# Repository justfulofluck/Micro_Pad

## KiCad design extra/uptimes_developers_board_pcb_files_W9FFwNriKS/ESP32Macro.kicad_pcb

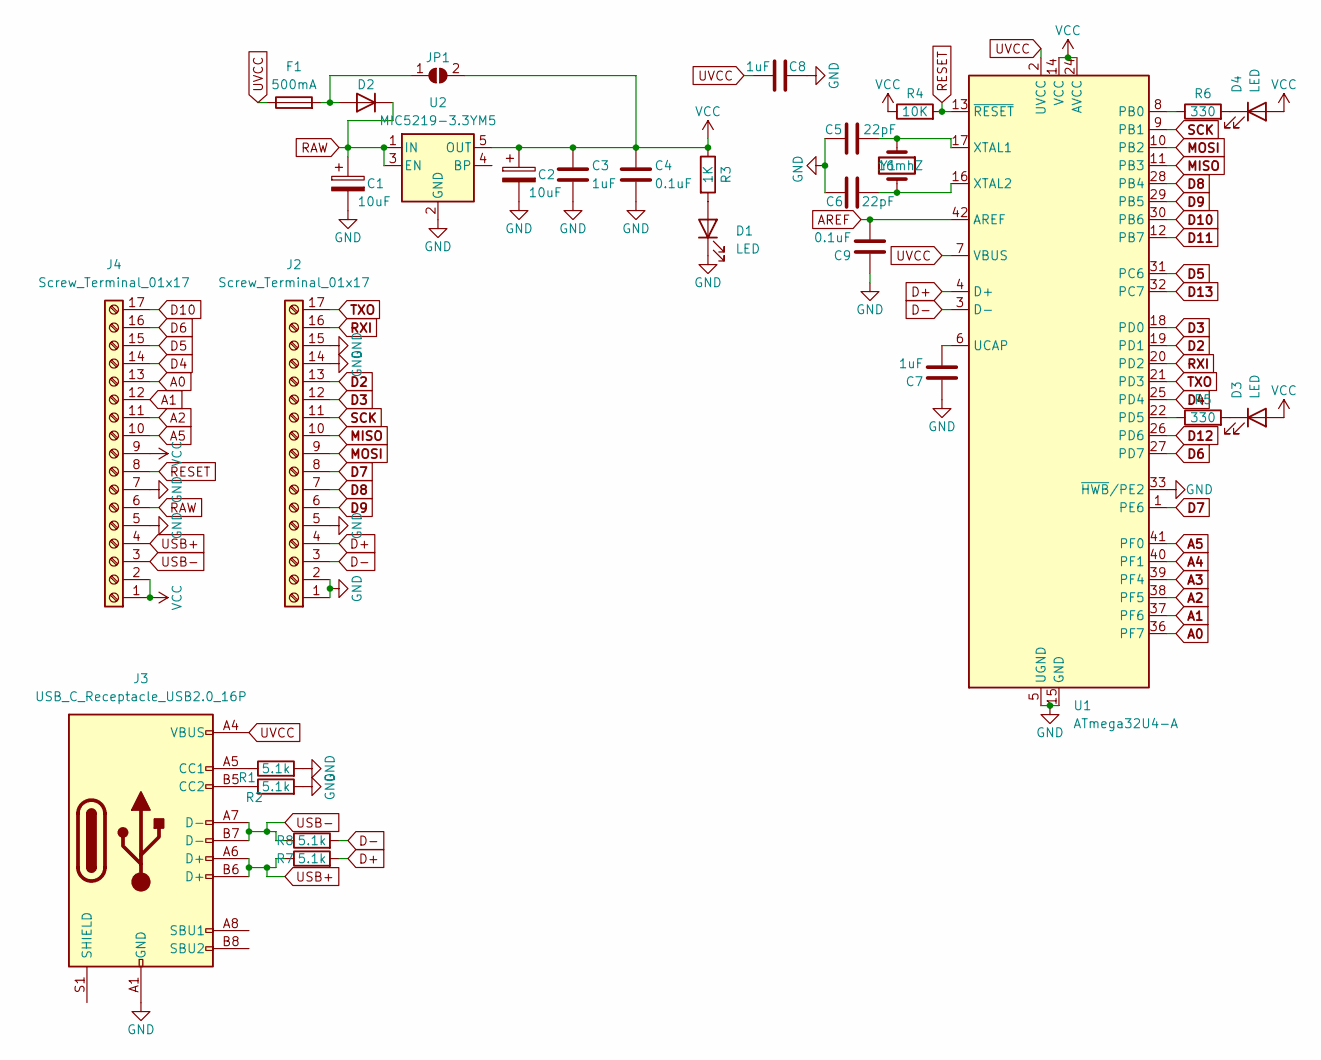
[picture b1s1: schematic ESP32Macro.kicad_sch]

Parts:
C1, C2: 10uF; CP_EIA-3216-18_Kemet-A
C3, C7, C8: 1uF; C_0402_1005Metric
C4, C9: 0.1uF; C_0402_1005Metric
C5, C6: 22pF; C_0402_1005Metric
D1, D3, D4: LED; LED_0805_2012Metric
D2: 1N4148WS; D_SOD-323
F1: 500mA; Fuse_1206_3216Metric
J2, J4: Screw_Terminal_01x17; PinHeader_1x17_P2.54mm_Vertical
J3: USB_C_Receptacle_USB2.0_16P; USB_C_Receptacle_GCT_USB4105-xx-A_16P_TopMnt_Horizontal
JP1: SolderJumper_2_Open; SolderJumper-2_P1.3mm_Open_RoundedPad1.0x1.5mm
R1, R2, R7, R8: 5.1k; R_0402_1005Metric
R3: 1K; R_0402_1005Metric
R4: 10K; R_0402_1005Metric
R5, R6: 330; R_0402_1005Metric
U1: ATmega32U4-A; TQFP-44_10x10mm_P0.8mm
U2: MIC5219-3.3YM5; SOT-23-5
Y1: 16mhZ; Crystal_SMD_3215-2Pin_3.2x1.5mm

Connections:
A0: J4.13, U1.36 (PF7)
A1: J4.12, U1.37 (PF6)
A2: J4.11, U1.38 (PF5)
A3: U1.39 (PF4)
A4: U1.40 (PF1)
A5: J4.10, U1.41 (PF0)
AREF: C9.2, U1.42 (AREF)
D2: J2.13, U1.19 (PD1)
D3: J2.12, U1.18 (PD0)
D4: J4.14, U1.25 (PD4)
D5: J4.15, U1.31 (PC6)
D6: J4.16, U1.27 (PD7)
D7: J2.8, U1.1 (PE6)
D8: J2.7, U1.28 (PB4)
D9: J2.6, U1.29 (PB5)
D10: J4.17, U1.30 (PB6)
D11: U1.12 (PB7)
D12: U1.26 (PD6)
D13: U1.32 (PC7)
D+: J2.4, R7.2, U1.4 (D+)
D-: J2.3, R8.2, U1.3 (D-)
GND: C1.2, C2.2, C3.2, C4.2, C5.1, C6.2, C7.1, C8.2, C9.1, D1.1 (K), J2.1, J2.2, J2.5, J2.14, J2.15, J3.A1 (GND), J3.A12 (GND), J3.B1 (GND), J3.B12 (GND), J4.5, J4.7, R1.2, R2.2, U1.5 (UGND), U1.15 (GND), U1.23 (GND), U1.33 (~HWB/PE2), U1.35 (GND), U1.43 (GND), U2.2 (GND)
MISO: J2.10, U1.11 (PB3)
MOSI: J2.9, U1.10 (PB2)
unnamed: D1.2 (A), R3.2
unnamed: D2.2 (A), F1.2, JP1.1 (A)
unnamed: D3.1 (K), R5.2
unnamed: D4.1 (K), R6.2
unnamed: J3.A5 (CC1), R1.1
unnamed: J3.B5 (CC2), R2.1
unnamed: R6.1, U1.8 (PB0)
unnamed: R5.1, U1.22 (PD5)
unnamed: C7.2, U1.6 (UCAP)
unnamed: C5.2, U1.17 (XTAL1), Y1.1
unnamed: C6.1, U1.16 (XTAL2), Y1.2
RAW: C1.1, D2.1 (K), J4.6, U2.1 (IN), U2.3 (EN)
RESET: J4.8, R4.2, U1.13 (~RESET)
RXI: J2.16, U1.20 (PD2)
SCK: J2.11, U1.9 (PB1)
TXO: J2.17, U1.21 (PD3)
USB+: J3.A6 (D+), J3.B6 (D+), J4.4, R7.1
USB-: J3.A7 (D-), J3.B7 (D-), J4.3, R8.1
UVCC: C8.1, F1.1, J3.A4 (VBUS), J3.A9 (VBUS), J3.B4 (VBUS), J3.B9 (VBUS), U1.2 (UVCC), U1.7 (VBUS)
VCC: C2.1, C3.1, C4.1, D3.2 (A), D4.2 (A), J4.1, J4.2, J4.9, JP1.2 (B), R3.1, R4.1, U1.14 (VCC), U1.24 (AVCC), U1.34 (VCC), U1.44 (AVCC), U2.5 (OUT)

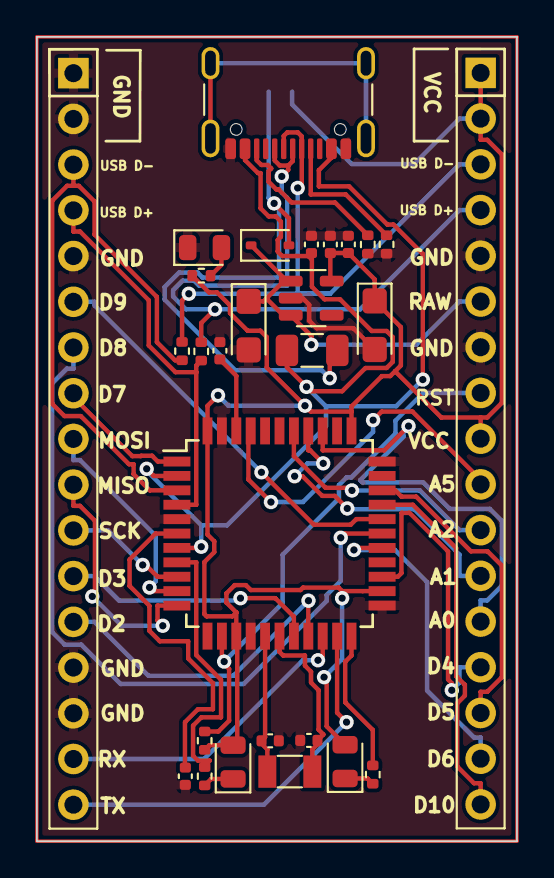
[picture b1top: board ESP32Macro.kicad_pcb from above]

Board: 2 copper layers, 26.7 x 44.7 mm, 29 parts (1 on the bottom side), 39 nets.

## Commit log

2024-09-09 code send
2024-09-12 Complete prototype code.
2024-09-12 added connection image with aurdio
2024-09-12 added reference
2024-09-15 added documnets
2024-09-16 added configuration files for proxmox
2024-09-21 extra folder
2024-10-01 added libraries and complementary code for project
2024-10-03 Added Base codes, and write Hardware Interactive CODE.
2024-10-08 Removed mode functions for now.
2024-10-13 structured code for hardware.
2024-10-14 added Firmware files in code.
2024-10-18 modify code for Atmega32UA
2024-10-20 GTK basre software development started added button and board indicator and macro list.
2025-03-08 endoer keypad.c
2025-03-09 Update keypad.c
    Add encoder stable code.
2025-04-05 remove unwanted items
